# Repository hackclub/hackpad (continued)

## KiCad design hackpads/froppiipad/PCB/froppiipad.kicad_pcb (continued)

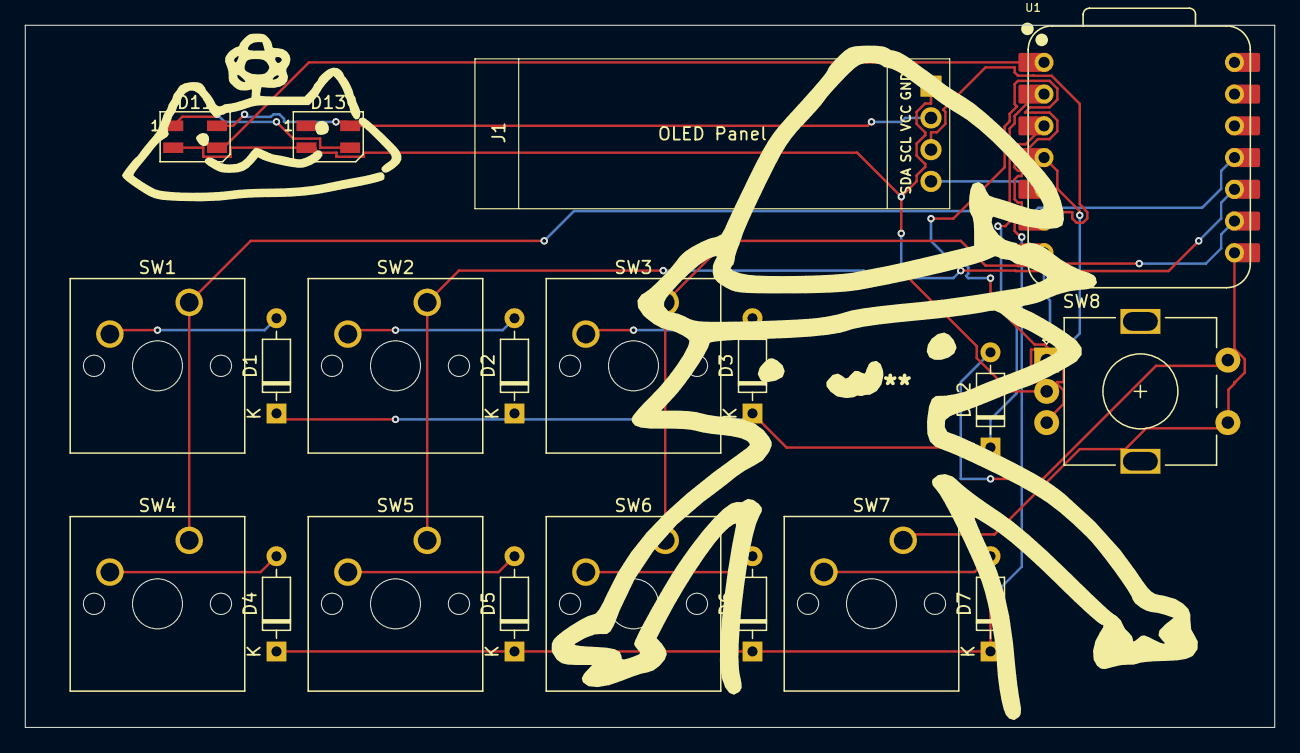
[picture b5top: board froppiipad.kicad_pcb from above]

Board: 2 copper layers, 100.0 x 56.2 mm, 20 parts (0 on the bottom side), 22 nets.

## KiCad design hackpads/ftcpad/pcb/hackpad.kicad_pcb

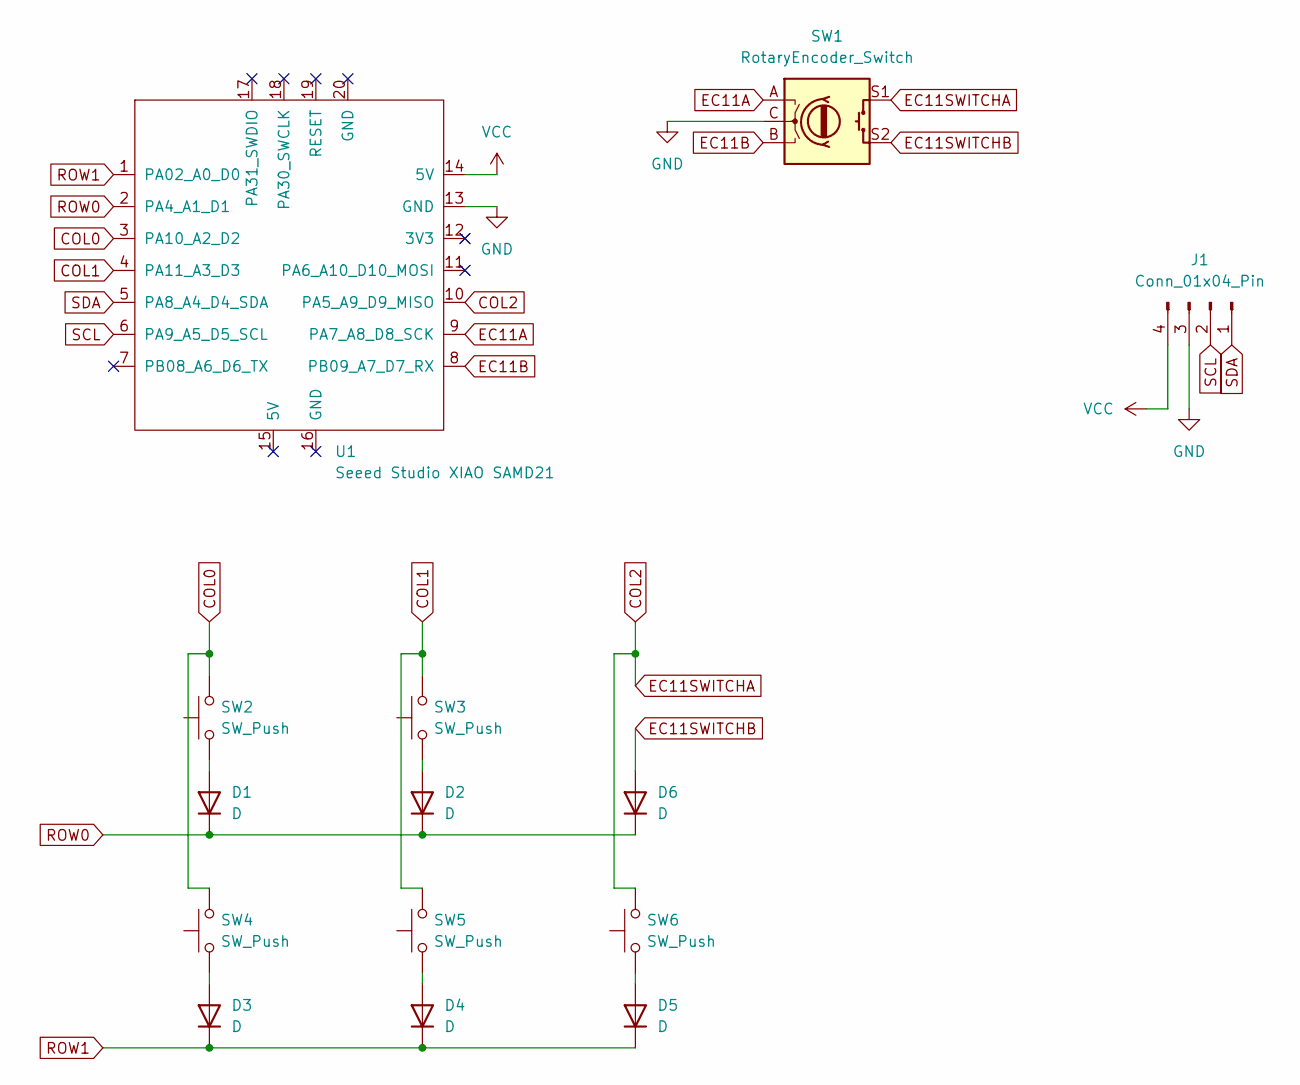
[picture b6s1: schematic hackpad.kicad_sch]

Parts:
D1, D2, D3, D4, D5, D6: D; D_DO-35_SOD27_P7.62mm_Horizontal
J1: Conn_01x04_Pin; PinHeader_1x04_P2.54mm_Vertical
SW1: RotaryEncoder_Switch; RotaryEncoder_Alps_EC11E-Switch_Vertical_H20mm
SW2, SW3, SW4, SW5, SW6: SW_Push; SW_Cherry_MX_1.00u_PCB
U1: Seeed Studio XIAO SAMD21; XIAO-Generic-Hybrid-14P-2.54-21X17.8MM

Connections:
COL0: SW2.2, SW4.2, U1.3 (PA10_A2_D2)
COL1: SW3.2, SW5.2, U1.4 (PA11_A3_D3)
COL2: SW1.S1, SW6.2, U1.10 (PA5_A9_D9_MISO)
EC11A: SW1.A, U1.9 (PA7_A8_D8_SCK)
EC11B: SW1.B, U1.8 (PB09_A7_D7_RX)
EC11SWITCHB: D6.2 (A), SW1.S2
GND: J1.3, SW1.C, U1.13 (GND)
unnamed: D1.2 (A), SW2.1
unnamed: D2.2 (A), SW3.1
unnamed: D3.2 (A), SW4.1
unnamed: D4.2 (A), SW5.1
unnamed: D5.2 (A), SW6.1
ROW0: D1.1 (K), D2.1 (K), D6.1 (K), U1.2 (PA4_A1_D1)
ROW1: D3.1 (K), D4.1 (K), D5.1 (K), U1.1 (PA02_A0_D0)
SCL: J1.2, U1.6 (PA9_A5_D5_SCL)
SDA: J1.1, U1.5 (PA8_A4_D4_SDA)
VCC: J1.4, U1.14 (5V)

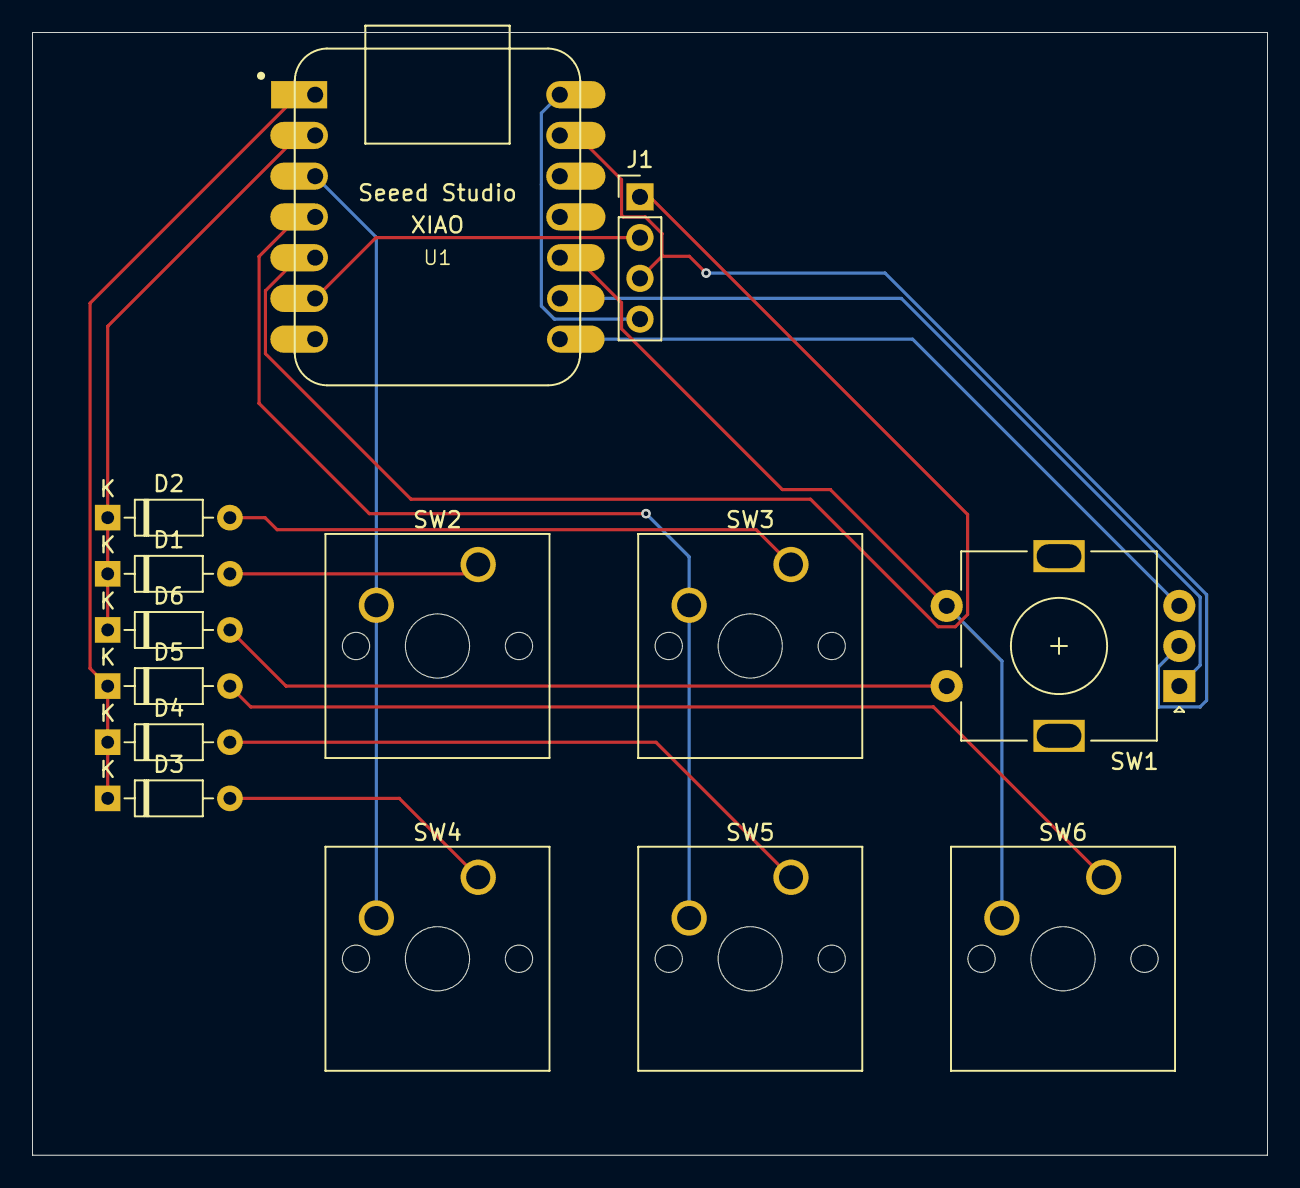
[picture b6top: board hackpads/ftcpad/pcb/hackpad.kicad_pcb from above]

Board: 2 copper layers, 77.0 x 70.0 mm, 14 parts (0 on the bottom side), 17 nets.
